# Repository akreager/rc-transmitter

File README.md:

# RC Transmitter
Open-source design and code for a 3D-printed pistol-grip RC transmitter.

## Overview
A general-purpose RC transmitter designed to control multiple vehicles by swapping configuration profiles. Currently used with an RC snowblower and an engineering test rover.

### Features
- **Wireless control** via nRF24L01+ with bidirectional telemetry (acknowledge payloads)
- **Touchscreen UI** on a 240x320 TFT with resistive touch input
- **Live telemetry** display: battery voltage, board temperatures, motor currents
- **Motor stop** (M-Stop) soft button on the touchscreen
- **Joystick input** for throttle and steering

### Planned
- Joystick calibration via touchscreen UI
- Physical button matrix (multiplexed)
- SD card configuration profiles for multi-vehicle support
- Settings/setup menu

## Hardware

### Transmitter
- MCU with dual SPI buses (currently Teensy 4.1)
- [Adafruit 2.8" TFT Touch Breakout](https://www.adafruit.com/product/1770) — ILI9341 display with resistive touchscreen (SPI1)
- nRF24L01+ radio module (SPI0)
- Analog joystick (steering + throttle)

### Receiver ([Rover Test Platform](https://github.com/akreager/roverTest))
- Arduino Mega
- nRF24L01+ radio module
- Basicmicro RoboClaw motor controller

## Project Structure
```
RC Transmitter/
├── main/                 # Transmitter firmware (Arduino IDE)
│   ├── main.ino          # Setup, loop, radio, global state
│   ├── config.h          # Pin assignments, constants, shared types
│   ├── touchInput.ino    # Touch state machine
│   ├── screenManager.ino # Screen transitions and button management
│   └── drawScreens.ino   # Screen drawing and UI updates
├── test_sketches/        # Standalone test/reference sketches
├── stl/                  # 3D printed enclosure files
├── docs/                 # Documentation and images
├── LICENSE               # GPLv3
└── README.md
```

## Pin Assignments (Teensy 4.1)

Active pin mapping for the current build. Also maintained in [Google Sheets](https://docs.google.com/spreadsheets/d/1aVeEQQCFw7_oekkrW9wztb_qrHcS88uQesicZp7ygn0/edit?gid=1983508387#gid=1983508387).

### Display & Touch (SPI1)
| Function | Pin  | Notes                   |
|----------|------|-------------------------|
| CLK      | D27  | SPI1 clock              |
| MISO     | D1   | SPI1 data in            |
| MOSI     | D26  | SPI1 data out           |
| TFT CS   | D0   | Display chip select     |
| TFT DC   | D2   | Display data/command    |
| Backlight| D3   | PWM brightness control  |
| Touch Y+ | D24  | Analog (A10)            |
| Touch X- | D25  | Analog (A11)            |
| Touch X+ | D28  | Digital                 |
| Touch Y- | D29  | Digital                 |

### Radio (SPI0)
| Function | Pin  | Notes                   |
|----------|------|-------------------------|
| SCK      | D13  | SPI0 clock (default)    |
| MISO     | D12  | SPI0 data in (default)  |
| MOSI     | D11  | SPI0 data out (default) |
| CE       | D9   |                         |
| CSN      | D10  |                         |

### Inputs
| Function  | Pin  | Notes                              |
|-----------|------|------------------------------------|
| Steering  | D14  | Analog (A0) — wheel input          |
| Throttle  | D15  | Analog (A1) — trigger input        |
| Joystick X| D17  | Analog (A3) — e.g. chute aim L/R  |
| Joystick Y| D16  | Analog (A2) — e.g. chute aim U/D  |

### Button Matrix (planned)
| Function | Pin  | Notes                  |
|----------|------|------------------------|
| Row A    | D30  | Digital                |
| Row B    | D31  | Digital                |
| Row C    | D32  | Digital                |
| Row D    | D33  | Digital                |
| Col 1    | D34  | Digital                |
| Col 2    | D35  | Digital                |

## CAD Source
3D design for the transmitter enclosure is on [OnShape](https://cad.onshape.com/documents/a59ab4c30cdb2f94f953abb2/v/0076fda3a5d6eca29f873ec9/e/06b2695cd32d304990fa8f74).

## Dependencies
Install via Arduino IDE Library Manager:
- [RF24](https://github.com/tmrh20/RF24/) (TMRh20 fork)
- [Adafruit GFX Library](https://github.com/adafruit/Adafruit-GFX-Library)
- [Adafruit ILI9341](https://github.com/adafruit/Adafruit_ILI9341)
- [Adafruit BusIO](https://github.com/adafruit/Adafruit_BusIO)

Bundled with the Teensy board package:
- TouchScreen — included in `{teensy_package}/libraries/TouchScreen`, API-compatible with [Adafruit TouchScreen](https://github.com/adafruit/Adafruit_TouchScreen)

Receiver also requires:
- [RoboClaw Arduino Library](https://github.com/basicmicro/roboclaw_arduino_library)

## Development
This project is developed with assistance from Claude (Anthropic), used for code architecture, refactoring, and documentation.

## License
This project is licensed under the GNU General Public License v3.0 — see [LICENSE](LICENSE) for details.

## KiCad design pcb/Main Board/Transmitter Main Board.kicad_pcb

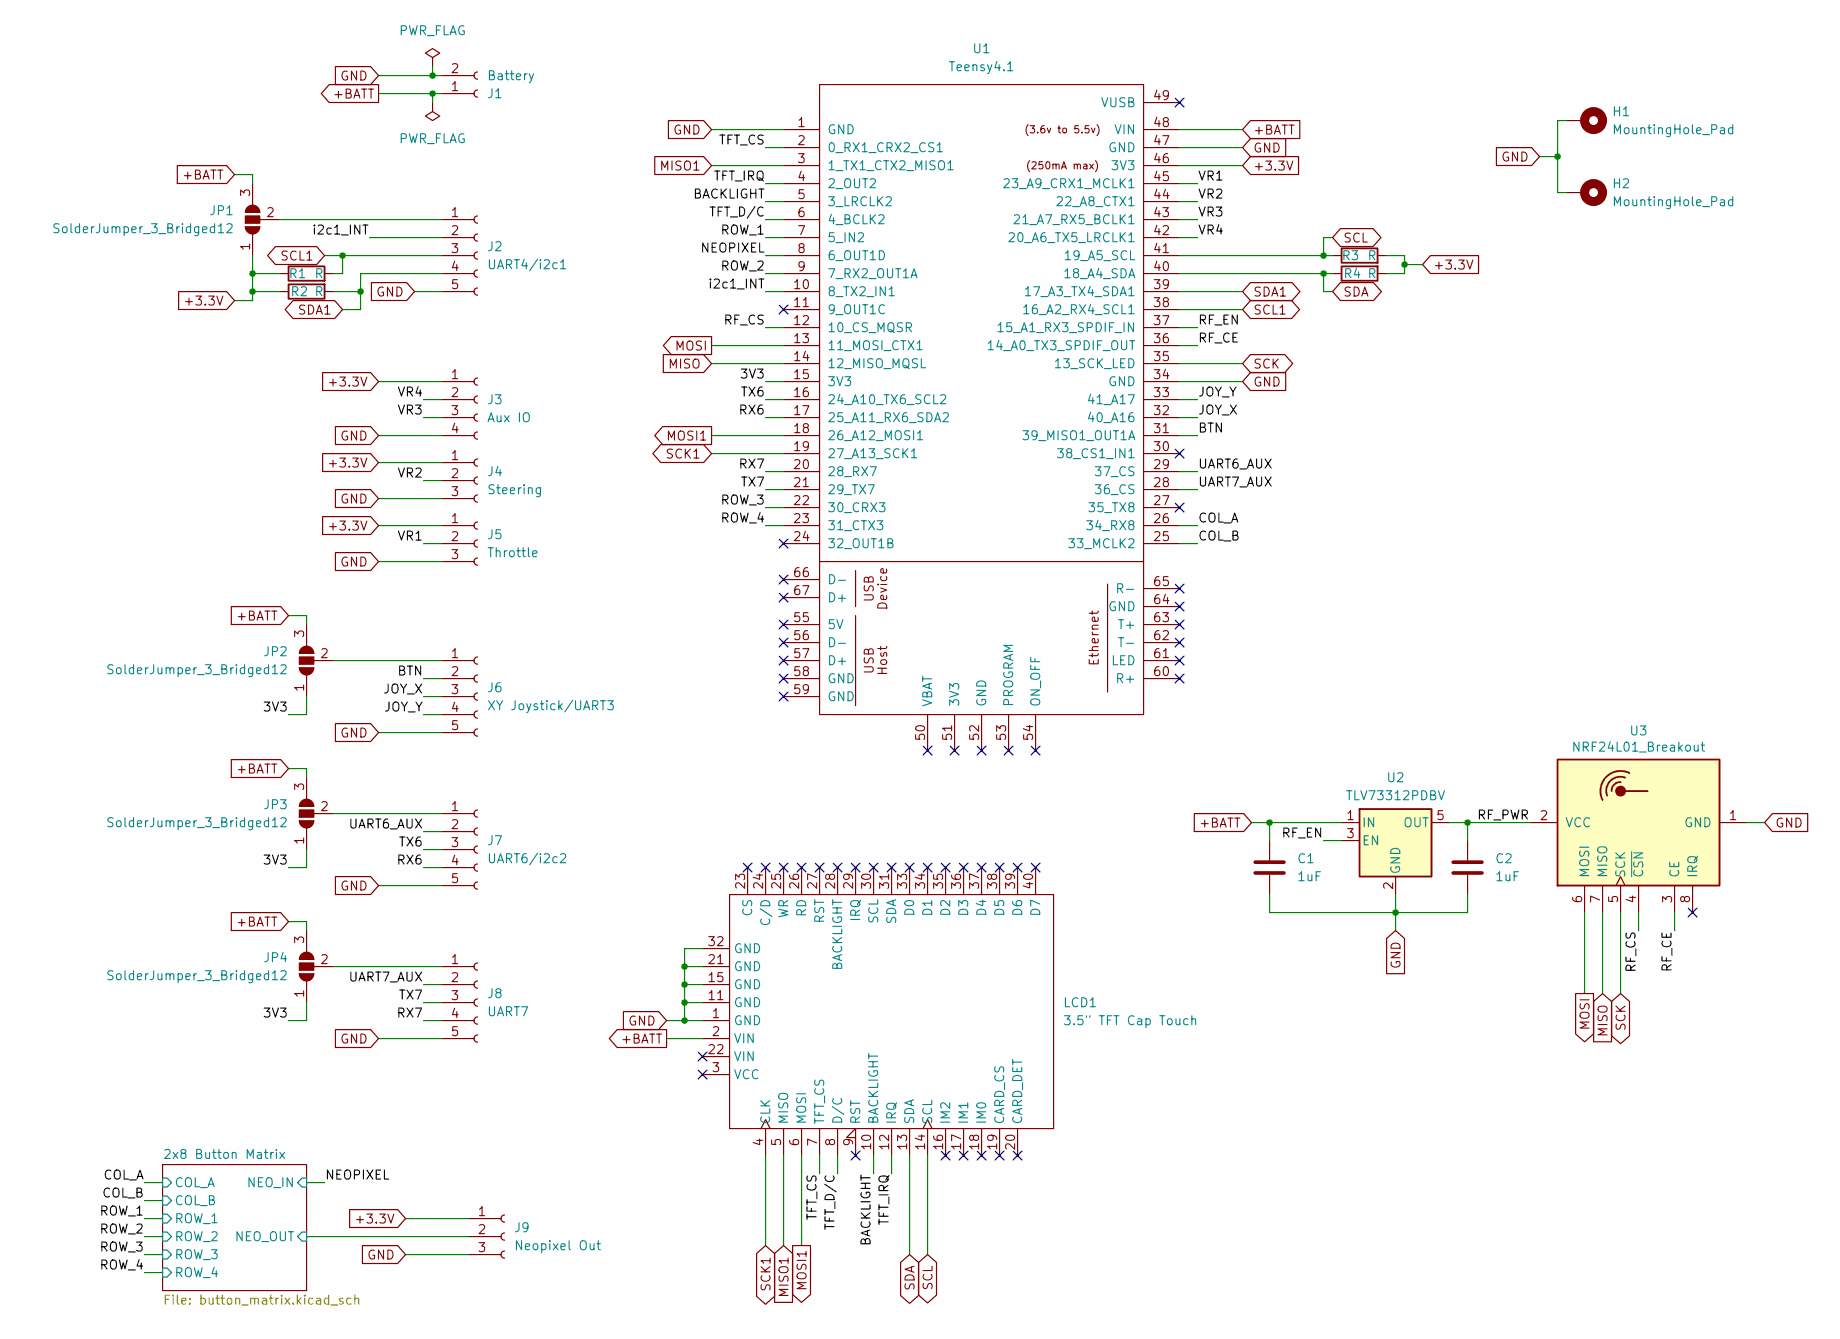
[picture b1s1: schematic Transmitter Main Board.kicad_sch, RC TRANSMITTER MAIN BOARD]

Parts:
C1, C2: 1uF; C_0805_2012Metric_Pad1.18x1.45mm_HandSolder
H1, H2: MountingHole_Pad; MountingHole_3.2mm_M3_Pad
J1: Battery; JST_PH_B2B-PH-K_1x02_P2.00mm_Vertical
J2: UART4/i2c1; JST_PH_B5B-PH-K_1x05_P2.00mm_Vertical
J3: Aux IO; JST_PH_B4B-PH-K_1x04_P2.00mm_Vertical
J4: Steering; JST_PH_B3B-PH-K_1x03_P2.00mm_Vertical
J5: Throttle; JST_PH_B3B-PH-K_1x03_P2.00mm_Vertical
J6: XY Joystick/UART3; JST_PH_B5B-PH-K_1x05_P2.00mm_Vertical
J7: UART6/i2c2; JST_PH_B5B-PH-K_1x05_P2.00mm_Vertical
J8: UART7; JST_PH_B5B-PH-K_1x05_P2.00mm_Vertical
J9: Neopixel Out; JST_PH_B3B-PH-K_1x03_P2.00mm_Vertical
JP1, JP2, JP3, JP4: SolderJumper_3_Bridged12; SolderJumper-3_P2.0mm_Open_TrianglePad1.0x1.5mm
LCD1: 3.5" TFT Cap Touch; Adafruit_3.5in_480x320_TFT_CapTouch
R1, R2, R3, R4: R; R_0805_2012Metric_Pad1.20x1.40mm_HandSolder
U1: Teensy4.1; Teensy41
U2: TLV73312PDBV; SOT-23-5
U3: NRF24L01_Breakout; nRF24L01_Breakout

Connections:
+3.3V: J3.1, J4.1, J5.1, J9.1, JP1.1 (A), R1.1, R2.1, R3.2, R4.2, U1.46 (3V3); also elsewhere on the board
+BATT: C1.1, J1.1, JP1.3 (B), JP2.3 (B), JP3.3 (B), JP4.3 (B), LCD1.2 (VIN), U1.48 (VIN), U2.1 (IN)
/2x8 Button Matrix/NEO_OUT: J9.2; also elsewhere on the board
/3V3: JP2.1 (A), JP3.1 (A), JP4.1 (A), U1.15 (3V3)
/BACKLIGHT: LCD1.10 (BACKLIGHT), U1.5 (3_LRCLK2)
/BTN: J6.2, U1.31 (39_MISO1_OUT1A)
/COL_A: U1.26 (34_RX8); also elsewhere on the board
/COL_B: U1.25 (33_MCLK2); also elsewhere on the board
/JOY_X: J6.3, U1.32 (40_A16)
/JOY_Y: J6.4, U1.33 (41_A17)
/NEOPIXEL: U1.8 (6_OUT1D); also elsewhere on the board
/RF_CE: U1.36 (14_A0_TX3_SPDIF_OUT), U3.3 (CE)
/RF_CS: U1.12 (10_CS_MQSR), U3.4 (~CSN)
/RF_EN: U1.37 (15_A1_RX3_SPDIF_IN), U2.3 (EN)
/RF_PWR: C2.1, U2.5 (OUT), U3.2 (VCC)
/ROW_1: U1.7 (5_IN2); also elsewhere on the board
/ROW_2: U1.9 (7_RX2_OUT1A); also elsewhere on the board
/ROW_3: U1.22 (30_CRX3); also elsewhere on the board
/ROW_4: U1.23 (31_CTX3); also elsewhere on the board
/RX6: J7.4, U1.17 (25_A11_RX6_SDA2)
/RX7: J8.4, U1.20 (28_RX7)
/TFT_CS: LCD1.7 (TFT_CS), U1.2 (0_RX1_CRX2_CS1)
/TFT_D/C: LCD1.8 (D/C), U1.6 (4_BCLK2)
/TFT_IRQ: LCD1.12 (IRQ), U1.4 (2_OUT2)
/TX6: J7.3, U1.16 (24_A10_TX6_SCL2)
/TX7: J8.3, U1.21 (29_TX7)
/UART6_AUX: J7.2, U1.29 (37_CS)
/UART7_AUX: J8.2, U1.28 (36_CS)
/VR1: J5.2, U1.45 (23_A9_CRX1_MCLK1)
/VR2: J4.2, U1.44 (22_A8_CTX1)
/VR3: J3.3, U1.43 (21_A7_RX5_BCLK1)
/VR4: J3.2, U1.42 (20_A6_TX5_LRCLK1)
/i2c1_INT: J2.2, U1.10 (8_TX2_IN1)
GND: C1.2, C2.2, H1.1, H2.1, J1.2, J2.5, J3.4, J4.3, J5.3, J6.5, J7.5, J8.5, J9.3, LCD1.1 (GND), LCD1.11 (GND), LCD1.15 (GND), LCD1.21 (GND), LCD1.32 (GND), U1.1 (GND), U1.34 (GND), U1.47 (GND), U2.2 (GND), U3.1 (GND); also elsewhere on the board
MISO: U1.14 (12_MISO_MQSL), U3.7 (MISO)
MISO1: LCD1.5 (MISO), U1.3 (1_TX1_CTX2_MISO1)
MOSI: U1.13 (11_MOSI_CTX1), U3.6 (MOSI)
MOSI1: LCD1.6 (MOSI), U1.18 (26_A12_MOSI1)
unnamed: J2.1, JP1.2 (C)
unnamed: J6.1, JP2.2 (C)
unnamed: J7.1, JP3.2 (C)
unnamed: J8.1, JP4.2 (C)
SCK: U1.35 (13_SCK_LED), U3.5 (SCK)
SCK1: LCD1.4 (CLK), U1.19 (27_A13_SCK1)
SCL: LCD1.14 (SCL), R3.1, U1.41 (19_A5_SCL)
SCL1: J2.3, R1.2, U1.38 (16_A2_RX4_SCL1)
SDA: LCD1.13 (SDA), R4.1, U1.40 (18_A4_SDA)
SDA1: J2.4, R2.2, U1.39 (17_A3_TX4_SDA1)

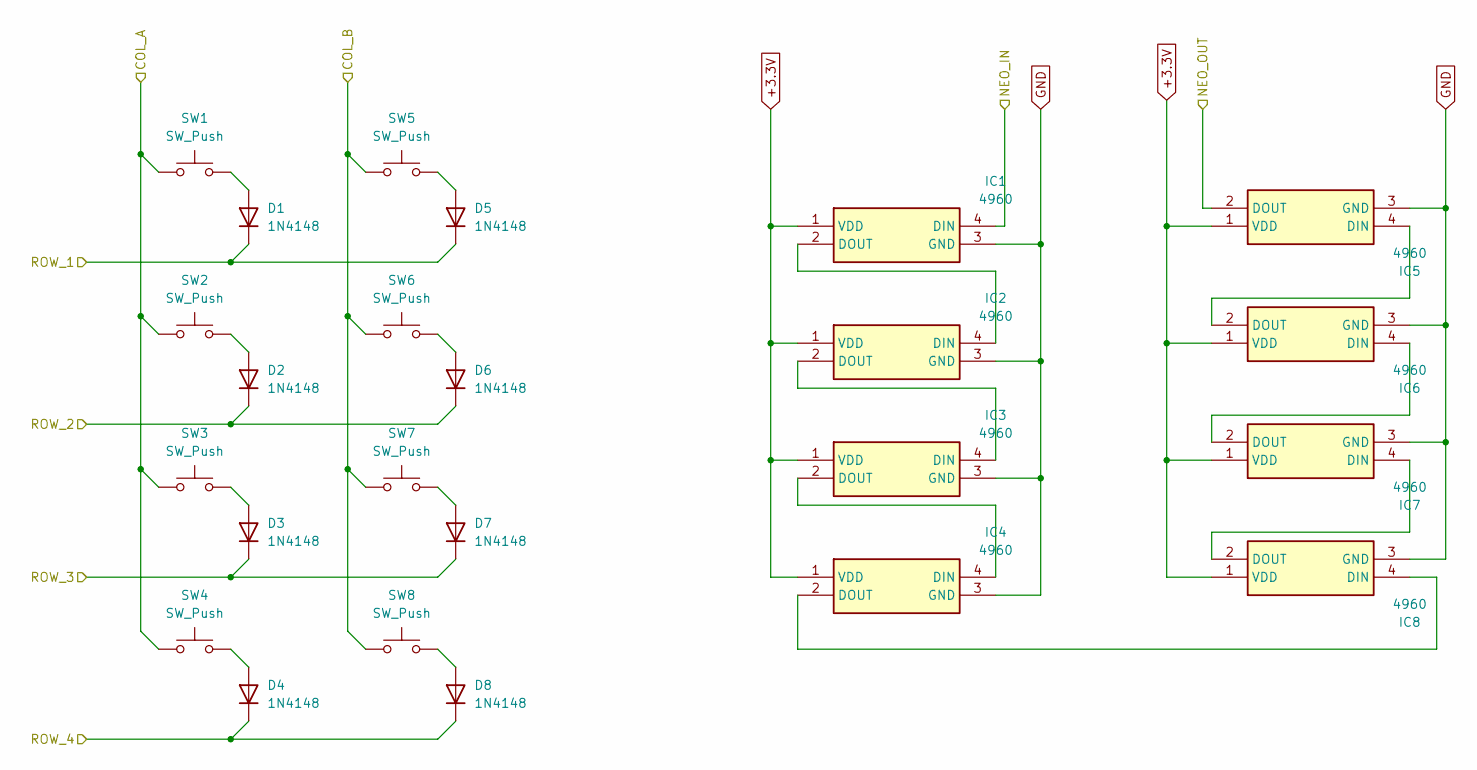
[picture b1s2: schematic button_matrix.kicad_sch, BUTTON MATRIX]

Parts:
D1, D2, D3, D4, D5, D6, D7, D8: 1N4148; D_SOD-123
IC1, IC2, IC3, IC4, IC5, IC6, IC7, IC8: 4960; 4960_ADA; Mouser Part Number 485-4960
SW1, SW2, SW3, SW4, SW5, SW6, SW7, SW8: SW_Push; SW_Kailh_Choc_V1

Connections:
+3.3V: IC1.1 (VDD), IC2.1 (VDD), IC3.1 (VDD), IC4.1 (VDD), IC5.1 (VDD), IC6.1 (VDD), IC7.1 (VDD), IC8.1 (VDD); also elsewhere on the board
/2x8 Button Matrix/NEO_OUT: IC5.2 (DOUT); also elsewhere on the board
/COL_A: SW1.1, SW2.1, SW3.1, SW4.1; also elsewhere on the board
/COL_B: SW5.1, SW6.1, SW7.1, SW8.1; also elsewhere on the board
/NEOPIXEL: IC1.4 (DIN); also elsewhere on the board
/ROW_1: D1.1 (K), D5.1 (K); also elsewhere on the board
/ROW_2: D2.1 (K), D6.1 (K); also elsewhere on the board
/ROW_3: D3.1 (K), D7.1 (K); also elsewhere on the board
/ROW_4: D4.1 (K), D8.1 (K); also elsewhere on the board
GND: IC1.3 (GND), IC2.3 (GND), IC3.3 (GND), IC4.3 (GND), IC5.3 (GND), IC6.3 (GND), IC7.3 (GND), IC8.3 (GND); also elsewhere on the board
unnamed: D1.2 (A), SW1.2
unnamed: D2.2 (A), SW2.2
unnamed: D3.2 (A), SW3.2
unnamed: D4.2 (A), SW4.2
unnamed: D5.2 (A), SW5.2
unnamed: D6.2 (A), SW6.2
unnamed: D7.2 (A), SW7.2
unnamed: D8.2 (A), SW8.2
unnamed: IC1.2 (DOUT), IC2.4 (DIN)
unnamed: IC2.2 (DOUT), IC3.4 (DIN)
unnamed: IC3.2 (DOUT), IC4.4 (DIN)
unnamed: IC4.2 (DOUT), IC8.4 (DIN)
unnamed: IC5.4 (DIN), IC6.2 (DOUT)
unnamed: IC6.4 (DIN), IC7.2 (DOUT)
unnamed: IC7.4 (DIN), IC8.2 (DOUT)

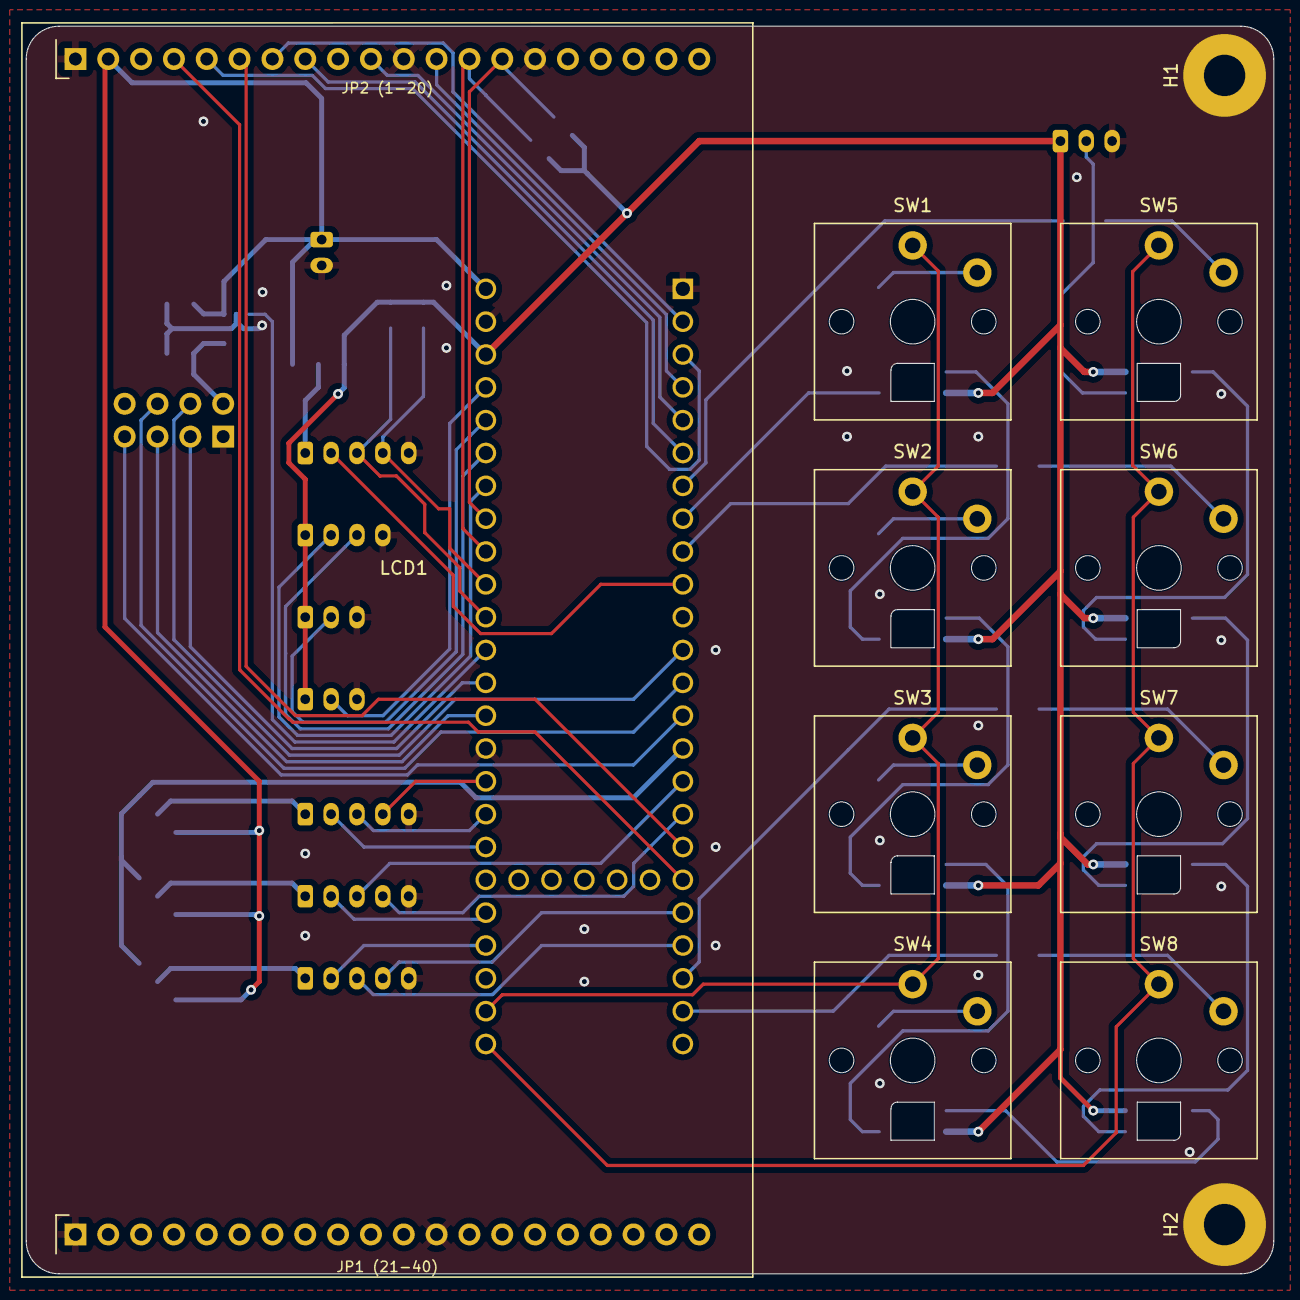
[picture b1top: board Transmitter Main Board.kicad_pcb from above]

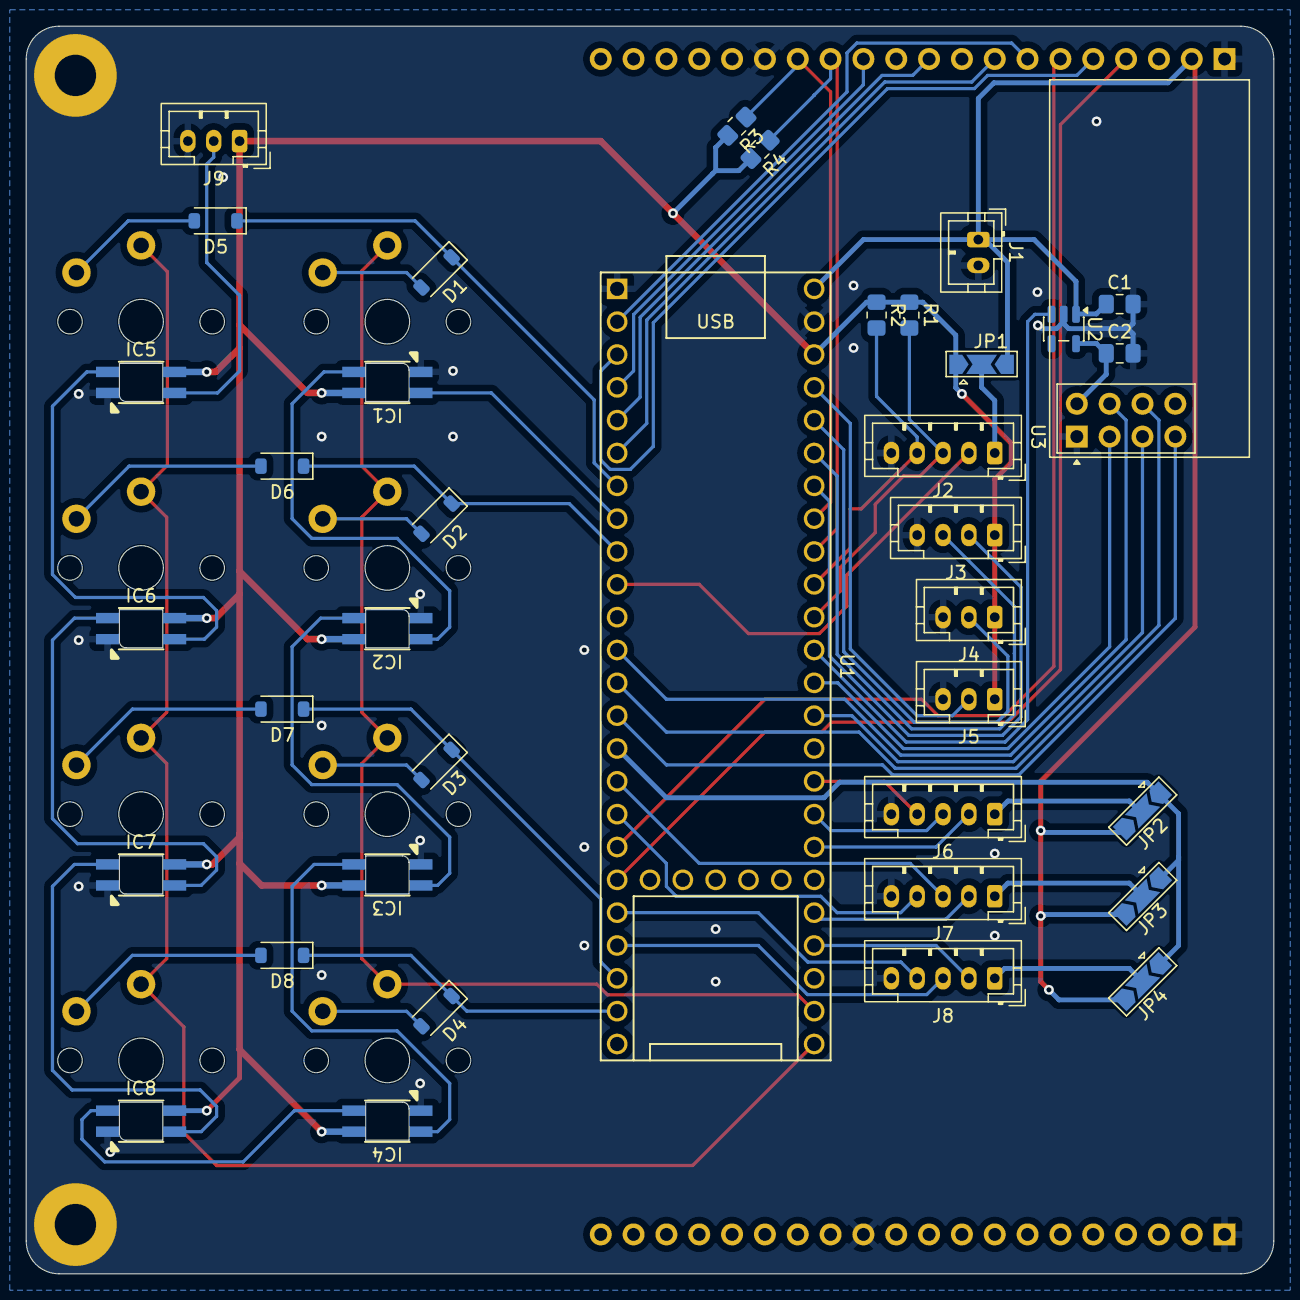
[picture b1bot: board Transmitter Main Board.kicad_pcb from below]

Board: 2 copper layers, 96.5 x 96.5 mm, 49 parts (30 on the bottom side), 63 nets.

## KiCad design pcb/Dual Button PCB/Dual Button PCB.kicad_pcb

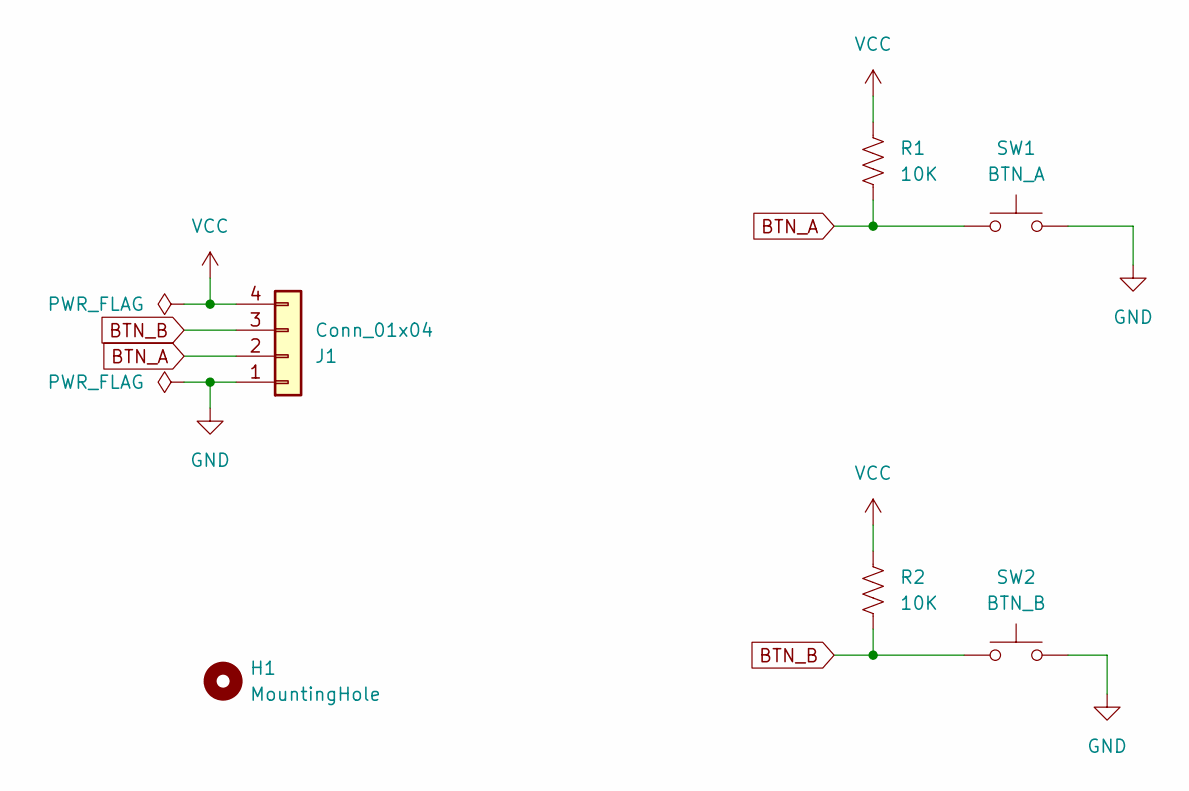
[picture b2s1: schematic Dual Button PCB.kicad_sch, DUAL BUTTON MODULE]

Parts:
H1: MountingHole; MountingHole_3.5mm
J1: Conn_01x04; JST_XH_B4B-XH-A_1x04_P2.50mm_Vertical
R1, R2: 10K; R_0805_2012Metric_Pad1.20x1.40mm_HandSolder
SW1: BTN_A; SW_PUSH_6mm_H5mm
SW2: BTN_B; SW_PUSH_6mm_H5mm

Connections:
BTN_A: J1.2, R1.1, SW1.1
BTN_B: J1.3, R2.2, SW2.2
GND: J1.1, SW1.2, SW2.1
VCC: J1.4, R1.2, R2.1

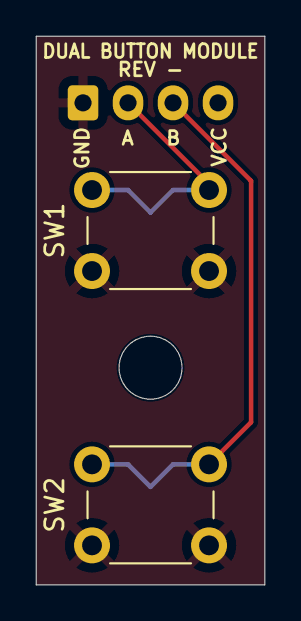
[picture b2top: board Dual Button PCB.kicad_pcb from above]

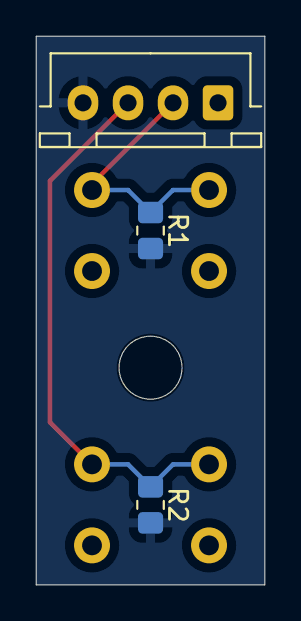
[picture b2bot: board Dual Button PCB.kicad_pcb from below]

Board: 2 copper layers, 12.7 x 30.5 mm, 6 parts (3 on the bottom side), 4 nets.

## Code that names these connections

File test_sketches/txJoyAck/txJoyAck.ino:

/*
  Optimized fork of nRF24L01 for Arduino & Raspberry Pi/Linux Devices:
  TMRh20/RF24, https://github.com/tmrh20/RF24/
  nRF24/RF24 is licensed under the
  GNU General Public License v2.0

  Based on:
  https://howtomechatronics.com/tutorials/arduino/arduino-wireless-communication-nrf24l01-tutorial/
  https://howtomechatronics.com/projects/diy-arduino-rc-transmitter/

  GFX example for the Adafruit ILI9341 Breakout and Shield
  ----> http://www.adafruit.com/products/1651
  Written by Limor Fried/Ladyada for Adafruit Industries.
  MIT license, all text above must be included in any redistribution
*/

#include <SPI.h>
#include <nRF24L01.h>
#include <RF24.h>
#include <Adafruit_BusIO_Register.h>
#include <Adafruit_SPIDevice.h>
#include <Adafruit_GFX.h>
#include <Adafruit_ILI9341.h>

//nRF24 pins hardware +SPI
#define CE_PIN 9
#define CSN_PIN 10
RF24 radio(CE_PIN, CSN_PIN);
const byte address[6] = "00001";

//The display uses hardware SPI1, plus #0 & #2
#define TFT_CS 0
#define TFT_DC 2
Adafruit_ILI9341 tft = Adafruit_ILI9341(&SPI1, TFT_DC, TFT_CS);

//Custom color definitions
#define SHADOW 0x2965

//Joystick pins
#define joy_X A0
#define joy_Y A1

unsigned int rawBatt = 185;
unsigned int rawTemp1 = 225;
unsigned int rawTemp2 = 231;
int rawCurrentMotor1 = 521;
int rawCurrentMotor2 = 482;

unsigned int oldBatt;
unsigned int oldTemp1;
unsigned int oldTemp2;
int oldCurrentMotor1;
int oldCurrentMotor2;

//package to contain outgoing data
struct dataPackage {
  byte throttle;
  byte steering;
  byte flag_motor_stop;
};
dataPackage data;

//package to contain incoming acknowledge data
struct ackPackage {
  byte highBatt;
  byte lowBatt;
  byte highTemp1;
  byte lowTemp1;
  byte highTemp2;
  byte lowTemp2;
  byte highIM1;
  byte lowIM1;
  byte highIM2;
  byte lowIM2;
};
ackPackage ack;

void setup() {
  tft.begin();
  tft.setRotation(2);
  drawHome();

  radio.begin();
  radio.openWritingPipe(address);
  radio.setDataRate(RF24_250KBPS);
  radio.setPALevel(RF24_PA_MIN);
  radio.enableAckPayload();
  radio.setRetries(3, 5);

  //set default data values
  data.throttle = 64;
  data.steering = 64;
}

void loop() {
  // put your main code here, to run repeatedly:
  data.throttle = map(analogRead(A1), 0, 1023, 127, 0);
  data.steering = map(analogRead(A0), 0, 1023, 0, 127);

  radio.write(&data, sizeof(dataPackage));
  if (radio.isAckPayloadAvailable() ) {
    radio.read(&ack, sizeof(ackPackage));

    //reconstitute acknowledge bytes
    rawBatt = (ack.highBatt << 8 ) + ack.lowBatt;
    rawTemp1 = (ack.highTemp1 << 8) + ack.lowTemp1;
    rawTemp2 = (ack.highTemp2 << 8) + ack.lowTemp2;
    rawCurrentMotor1 = (ack.highIM1 << 8) + ack.lowIM1;
    rawCurrentMotor2 = (ack.highIM2 << 8) + ack.lowIM2;

    //convert received tenths/hundredths data to whole numbers
    int mainBattery = rawBatt / 10;
    int temp1 = rawTemp1 / 10;
    int temp2 = rawTemp2 / 10;
    int currentM1 = rawCurrentMotor1 / 100;
    int currentM2 = rawCurrentMotor2 / 100;

    tft.setTextSize(3);
    tft.setTextColor(ILI9341_GREEN, ILI9341_BLACK);

    //print battery value
    tft.setCursor(112, 30);
    tft.print(mainBattery);
    tft.print(".");
    tft.print(rawBatt - (mainBattery * 10));
    tft.print("V ");

    //print temp1 value
    tft.setCursor(112, 54);
    tft.print(temp1);
    tft.print(".");
    tft.print(rawTemp1 - (temp1 * 10));
    tft.print((char)247);
    tft.print("C ");

    //prtin temp2 value
    tft.setCursor(112, 78);
    tft.print(temp2);
    tft.print(".");
    tft.print(rawTemp2 - (temp2 * 10));
    tft.print((char)247);
    tft.print("C ");

    //print M1 current value
    tft.setCursor(80, 126);
    tft.print(currentM1);
    tft.print(".");
    tft.print(rawCurrentMotor1 - (currentM1 * 100));
    tft.print("A ");

    //print M2 current value
    tft.setCursor(80, 174);
    tft.print(currentM2);
    tft.print(".");
    tft.print(rawCurrentMotor2 - (currentM2 * 100));
    tft.print("A ");
  }
}

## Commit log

2020-08-17 Initial migration from Arduino IDE to PlatformIO/VS Code
2020-08-17 Add current 3D stl files and link to 3D design source
2020-08-17 images added
2020-08-17 Add image
2020-08-25 Change pins for teensy 4.1
2021-04-16 begin adding motor stop flags
2021-04-16 recreate Arduino version
2021-04-16 add old test code
2021-04-19 Create calibration.ino
    sketch to calibrate analog inputs with a mechanical return-to-center, such as a joystick.
2021-04-19 add source/inspiration for code
2021-04-19 Update deadzone variables
    replace 'steering' and 'throttle' with 'wheel' and 'trigger'.
2026-02-08 reviving old project
2026-02-08 Revive project: restructure for Arduino IDE, add touchscreen UI framework
    Port from PlatformIO/VS Code to Arduino IDE multi-file project structure.
    Replace single main.cpp with modular .ino files:
    - main.ino: setup, loop, radio, global state
    - config.h: pin assignments, constants, shared types
    - touchInput.ino: resistive touch state machine with ghost-press prevention
    - screenManager.ino: screen transitions, button registration, hit testing
2026-02-08 Change documentation to point to bundled Touchscreen library.
2026-02-08 add cooldown for touch events
2026-02-09 incorporate new calibration routines
2026-02-16 Update .gitignore
    add kicad exclusions
2026-02-16 Add button board pcb project
2026-02-16 Start main pcb design
2026-02-17 files saved in the wrong directory
2026-02-17 Create 4960 symbol and footprint
2026-02-20 Python script to locate leds in relation to their switches.
2026-02-20 more routing
2026-02-21 more more more routing
2026-02-21 finalish routing
2026-02-22 Final final routing
2026-02-22 begin overcomplication
2026-02-25 export neutral formats
